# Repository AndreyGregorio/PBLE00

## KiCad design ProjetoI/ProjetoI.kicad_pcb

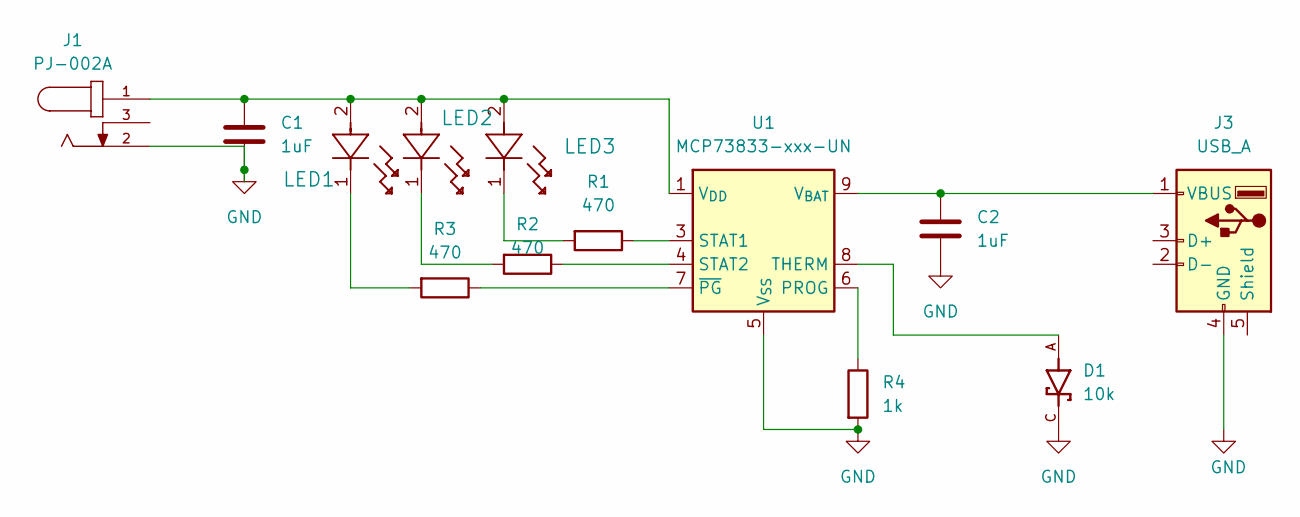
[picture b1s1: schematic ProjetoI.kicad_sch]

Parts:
C1, C2: 1uF; C_0805_2012Metric
D1: 10k; SOD3715X145N; PARTREV 18-2
J1: PJ-002A; CUI_PJ-002A
J3: USB_A; USB_A_Molex_67643_Horizontal
LED1, LED2, LED3: LED_LTST-C150GKT_LTO
R1, R2, R3: 470; R_0805_2012Metric
R4: 1k; R_0805_2012Metric
U1: MCP73833-xxx-UN; MSOP-10_3x3mm_P0.5mm

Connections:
GND: C1.2, C2.2, D1.C, J1.2, J3.4 (GND), R4.2, U1.5 (V_{SS})
unnamed: C1.1, J1.1, LED1.2, LED2.2, LED3.2, U1.1 (V_{DD}), U1.2 (V_{DD})
unnamed: C2.1, J3.1 (VBUS), U1.9 (V_{BAT}), U1.10 (V_{BAT})
unnamed: LED1.1, R3.2
unnamed: LED2.1, R2.2
unnamed: LED3.1, R1.2
unnamed: R4.1, U1.6 (PROG)
unnamed: R1.1, U1.3 (STAT1)
unnamed: R2.1, U1.4 (STAT2)
unnamed: D1.A, U1.8 (THERM)
unnamed: R3.1, U1.7 (~PG)

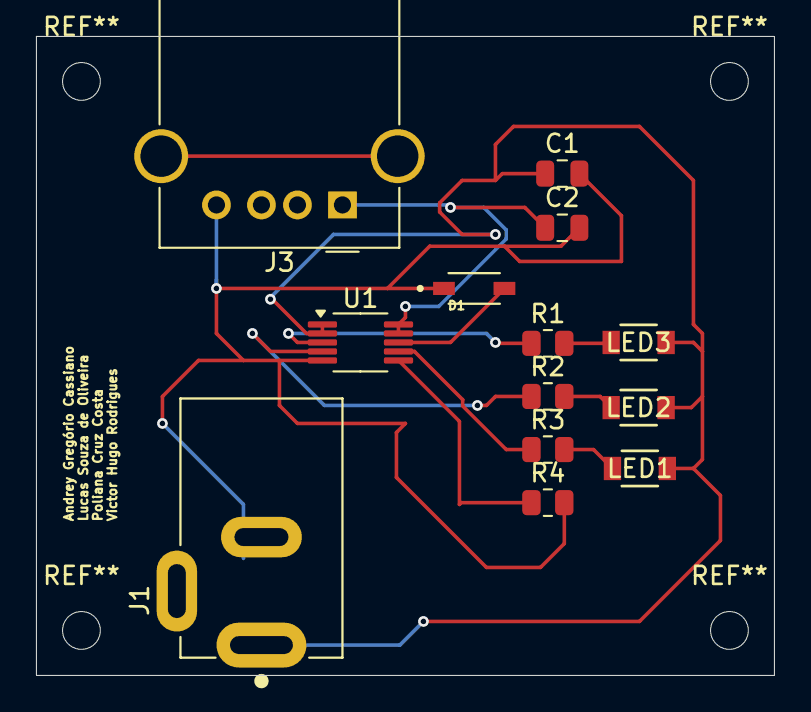
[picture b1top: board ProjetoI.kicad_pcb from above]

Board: 2 copper layers, 41.0 x 35.5 mm, 13 parts (0 on the bottom side), 11 nets.

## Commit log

2025-10-30 buracosv2
2025-11-28 novas imagens e modificações
2025-12-05 final
